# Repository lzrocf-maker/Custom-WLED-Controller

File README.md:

# Custom WLED Controller (ESP32-C3)

This is a custom board with an esp32 c3 as a brain for WLED projects or installations. Here is a photo of how the WLED Controller is suposed to look like when assembled:

## Project Overview
I have built this board to have more flexibility when making custom lighting projects, although it can also be used to control servos or whatever components require a data pin and voltaje.

## Hardware Specifications
- **Microcontroller:** ESP32-C3-Mini
- **Connectors:** 6x JST-Connectors, 1x Barrel-Jack 2.5mm, 1x Terminal-Block.
- **DC-DC Converter:** 1x 560Mini (If you can't find it, in the BOM there's a link to the amazon product).
- **Mounting:** 3x M3 screws, and two 3d printed halves.

## Board Screenshots
As shown in the images, 2 of the JST connectors are connected to the 5v output of the DC-DC converter, these two ports are for accessories.
The pinout reference is this:
- JST1 -> GPIO7
- JST2 -> GPIO8
- JST3 -> GPIO9
- JST4 -> GPIO10
- JST5 -> GPIO20
- JST6 -> GPIO21

## 3D Enclosure & Assembly
I designed the case so that you only have to print 2 parts, the two halves come together with 3 M3 screws that thread to the plastic with the PCB in the middle:

- **Top Plate:** I designed the top part so that you have the cut-outs for the barrel jack, terminal block and usb-c from the esp32-c3, as well as having the cut-outs for the 6 JST connectors.
  
- **Bottom Base:** The bottom part features a recesed part so that the pins of the components do not crash onto the case. It also has 3 countersunc holes for the 3 M3 screws.

## Firmware
This board uses WLED as the primary software, however, you can put any firmware you want that works with the configuration.

## Repository Contents
- The files ended on .kicad_sch/pro/pcb are the PCB files.
- The Gerbers.zip contains the files for PCB manufacturing.
- WLED LED Controller.step contains the 3d model of the macropad.
- There is a file named Code in the folder firmware that includes a code to test the leds, it blinks them from blue to red so you can make sure it works.
- The BOM file contains all the list of materials needed for manufacturing this project.

## This is the total price and components from aliexpress, along with the pcb:

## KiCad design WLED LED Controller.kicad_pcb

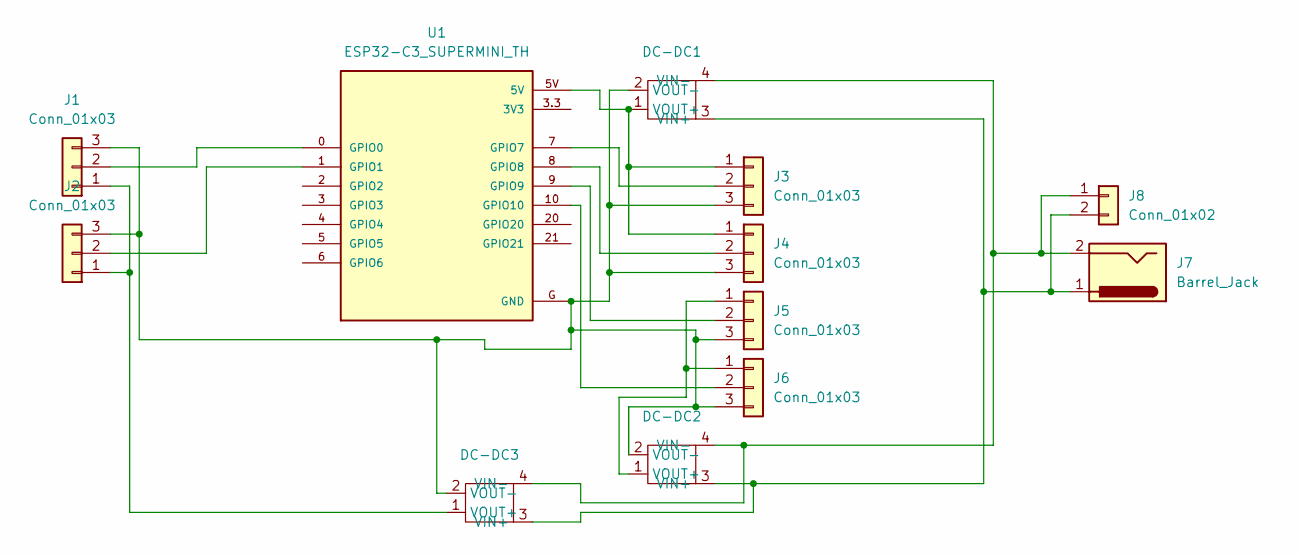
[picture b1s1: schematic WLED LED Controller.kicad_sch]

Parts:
DC-DC1, DC-DC2, DC-DC3: Mini560
J1, J2, J3, J4, J5, J6: Conn_01x03; JST_PH_B3B-PH-K_1x03_P2.00mm_Vertical
J7: Barrel_Jack; BarrelJack_Horizontal
J8: Conn_01x02; TerminalBlock_Phoenix_PT-1,5-2-5.0-H_1x02_P5.00mm_Horizontal
U1: ESP32-C3_SUPERMINI_TH; MODULE_ESP32-C3_SUPERMINI_TH

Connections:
unnamed: DC-DC1.3 (VIN+), DC-DC2.3 (VIN+), DC-DC3.3 (VIN+), J7.1, J8.2
unnamed: DC-DC1.4 (VIN-), DC-DC2.4 (VIN-), DC-DC3.4 (VIN-), J7.2, J8.1
unnamed: DC-DC1.1 (VOUT+), J3.1, J4.1, U1.5V
unnamed: DC-DC1.2 (VOUT-), DC-DC2.2 (VOUT-), DC-DC3.2 (VOUT-), J1.3, J2.3, J3.3, J4.3, J5.3, J6.3, U1.G (GND)
unnamed: DC-DC2.1 (VOUT+), J5.1, J6.1
unnamed: DC-DC3.1 (VOUT+), J1.1, J2.1
unnamed: J1.2, U1.0 (GPIO0)
unnamed: J2.2, U1.1 (GPIO1)
unnamed: J3.2, U1.7 (GPIO7)
unnamed: J4.2, U1.8 (GPIO8)
unnamed: J5.2, U1.9 (GPIO9)
unnamed: J6.2, U1.10 (GPIO10)

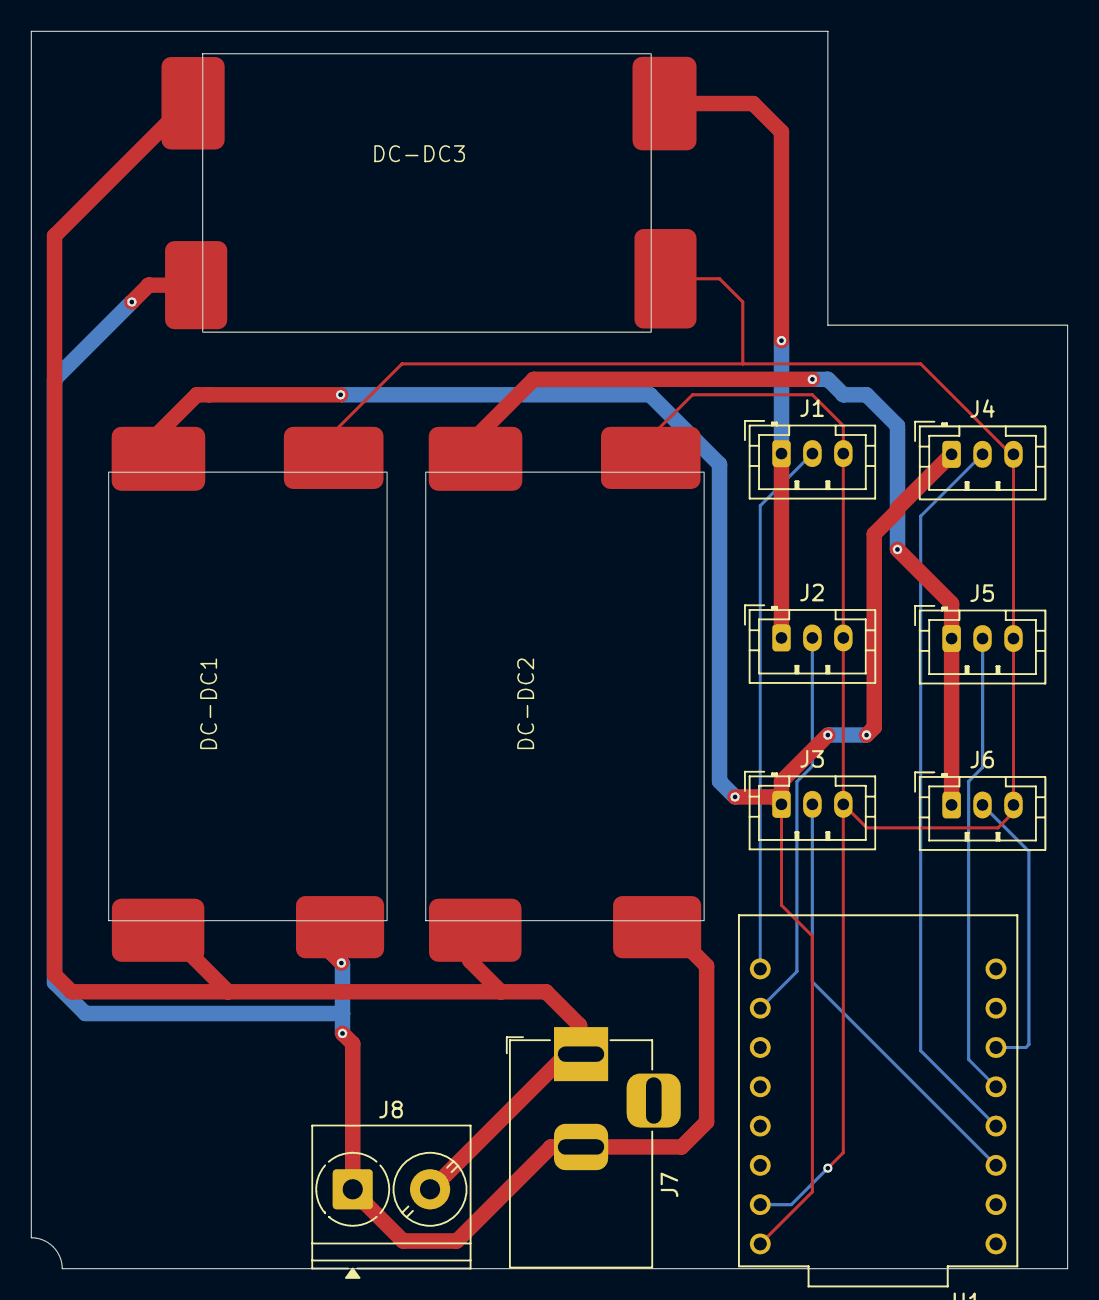
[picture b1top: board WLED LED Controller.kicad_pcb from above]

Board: 2 copper layers, 67.0 x 80.0 mm, 12 parts (0 on the bottom side), 12 nets.

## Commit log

2026-01-27 Update README with JST connector pinout
    Added pinout reference for JST connectors.
2026-02-16 Update print statement from 'Hello' to 'Goodbye'
2026-02-28 Add image to README for project visualization
    Added an image to the README for better visualization.
2026-02-28 Add LED control code using Adafruit NeoPixel library
2026-02-28 Refactor LED setup and color wipe functions
2026-02-28 Include total price and components from AliExpress
    Added pricing and component images from AliExpress.
